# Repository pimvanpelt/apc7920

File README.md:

# APC7920 based on ESP32

This is a project that replaces the older and unmaintained microcontroller
units in APC's famous rack PDU, the AP7920.

## Intro to AP7920

The AP7920 is an 8-port switchable rack mounted power distribution unit. It
features three main components:

1.  A power supply board, which has two 24V power supplies (PSU1 and PSU2) and
    three current sensors (Phase A, B and C). Each current sensor measures
    current from 0..30A AC. When sold in Europe, only one of these is used
    (Phase B).
1.  A microcontroller, based on an older Atmel chip, which features serial
    via an RJ12 plug, and 10/100 Ethernet via an RJ45 plug, and a 7-segment
    display which shows load on Phase B.
1.  A relay board, which features a general purpose I2C GPIO expander based on
    PCF8574, and eight 24V relays, one for each port on the front.

The design of this PDU is rather well done, with two power supplies, and a 
decoupled control plane. The wiring is of high quality, even after many
years of service the components are still in pristine shape. Shrink wrap
is used on the wiring for extra safety and the solder quality is very high.

If the microcontroller reboots or fails, the I2C GPIO expander stays put.
This allows operators to upgrade/reboot/tinker-with the management board
without interrupting service to the load.

### Pinouts

#### Power Supply Board

The power supply board has a 10-pin 2mm pitch connector. It exposes the two
24V power supplies, each with their own ground, and the three current sensors,
with their own separate common ground.

The black wire on the ribbon cables is Pin1. 

Pin | Meaning | Pin | Meaning
--- | --- | --- | ---
1 | I-Sens Phase C | 2 | I-Sens GND
3 | I-Sens Phase A | 4 | I-Sens GND
5 | +24V PSU1 | 6 | +24V PSU1
7 | I-Sens Phase B | 8 | GND PSU1
9 | GND PSU2 | 10 | +24V PSU2

It's worth pointing out that on the power supply board, all ground planes
are separated (so there's one ground pin for PSU1, one for PSU2 and one for
the current sensors).

#### Relay Board

The relay board has a 10-pin 2mm pitch connector. It exposes the I2C chip
which takes common `SDA`, `SDL`, `3.3V` and `GND` pins, and exposes three
address pins `ADDR0`, `ADDR1`, and `ADDR2`. This is presumably done so that
the microcontroller can address up to 8 of these relay boards. It also takes
24V in, which is used to drive the relays.

Pin | Meaning | Pin | Meaning
--- | --- | --- | ---
1 | GND | 2 | GND
3 | VDD (3.3V) | 4 | SDA
5 | +24V | 6 | +24V
7 | ADDR0 | 8 | SDL
9 | ADDR1 | 10 | ADDR2

AP7920 only has one expander, so it doesn't really matter which address
the MCU selects.

## Interposer board

This project works by replacing the two ribbon cables that go from the power
supply board and the relay board to the microcontroller. It's designed to
be a plugin replacement -- just remove the connectors from the microcontroller
and plug them into the interposer board instead.

The interposer has a few components. Firstly, there's a DC/DC buck converter
which takes 24V from PSU1 and switches it down to 5V. Then, there's a LDO that
takes the 5V and regulates it down to 3.3V. Lastly, there's an ADC chip that
measures the current on Phase A,B,C and the voltage out of PSU1 and PSU2 by 
using voltage dividers (the ADC runs at 3.3V so at least a 7:1 divider is
necessary to measure the 24V coming out of the PSUs). The 24V rail from PSU2
is looped through to the relay board. It exposes its 3.3V rail to the relay
board as well, to power the GPIO expander and a few other components there.

It exposes its ADC chip on the SPI header (taking `CS`, `CLK`, `DI` and `DO`)
and it exposes the GPIO expander from the relay board on the I2C header
(showing `SDA`, `SDL`). It offers the 5V and 3.3V rails on the PWR header.
This is enough to connect any other microcontroller that speaks I2C and SPI
instead of the microcontroller that comes with the AP7920 itself. The
interposer assumes only one PCF8574 chip, so it ties all three address pins
`ADDR0`, `ADDR1` and `ADDR2` to `GND`.

The interposer also ties `GND` together from both PSUs, as the original
microcontroller also does that. It has a solder pad (J4) that allows the
current sensor ground to be tied to the main ground as well. In production,
all four solder pads (J1..J4) should be soldered closed. This connects the
current sensor output to the ADC. You can measure the voltage between J4
and J1..J3 to see the current sensed on Phase A..C.

**NOTE** - There is a design flaw in the PCB as it assumes the current
sensor common should be tied to ground, which is not the case. It should be
tied to `VCC/2` so that the signal of the current transformer outputs hovers
between 0-3.3V instead of -1.65-1.65V. A new version is upcoming :)

### BOM

The following components are readily available on Mouser and Digikey. The
full bill of materials for the interposer is as such:

*   R1,R3: 10K Ohm -- voltage divider
*   R2,R4: 75K Ohm -- voltage divider (7:1 minimum)
*   R5,R6: 10K Ohm -- pullup for I2C, optional
*   R7: 220 Ohm -- for blue LED
*   D1: Blue LED 
*   C1: 22uF Tantalum 35V
*   C2,C3: 10uF Tantalum 16V
*   U1: MCP3208 -- 150mil SOIC (Microchip)
*   U2: TSR1-2450 (Traco Power)
*   X1, X2: 5x2 pin 2mm spaced header
*   J1, J2: 3x1 pin 2.54mm spaced header
*   J3: 5x1 pin 2.54mm spaced header

## ESP32 / ESP8266

There are two chips we have to interface with:

*   MCP3208 [datasheet](media/MCP3208.pdf); [driver](https://github.com/mongoose-os-libs/mcp320x-spi)
*   PCF8574 [datasheet](media/PCF8574.pdf); [driver](https://github.com/mongoose-os-libs/pcf8574-i2c)

Libraries for these two chips are readily available for Arduino, but I've
ported them as well to [Mongoose OS](https://mongoose-os.com/) which is my
development platform of choice. This makes writing the program really easy.

### Source Code

See the [firmware](firmware/README.md) directory for information on the firmware.

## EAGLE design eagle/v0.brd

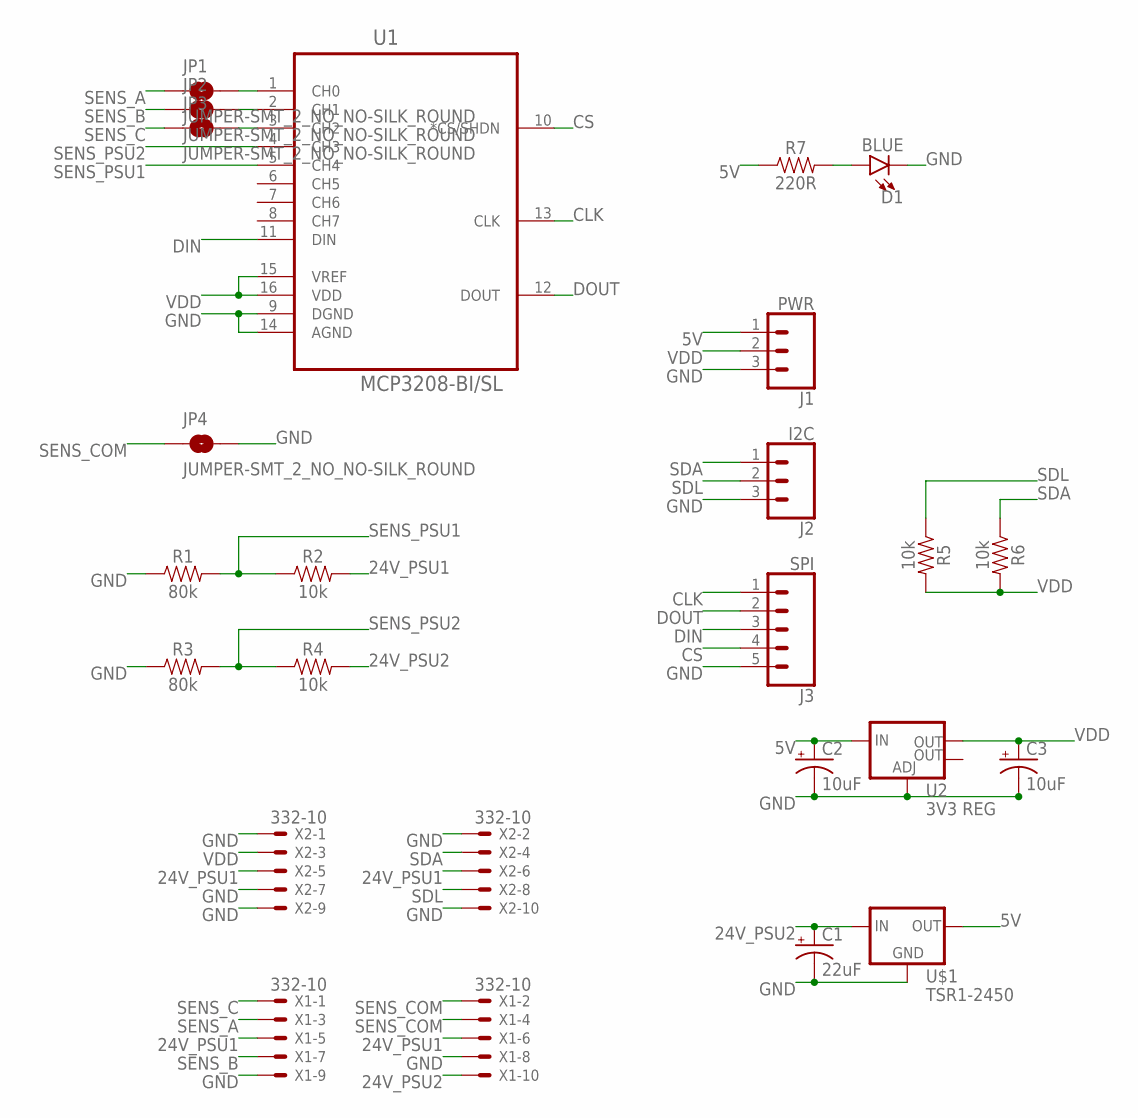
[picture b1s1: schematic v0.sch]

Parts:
C1: 22uF; EIA3216
C2, C3: 10uF; EIA3216
D1: BLUE; LED-0603
J1: PWR; 1X03
J2: I2C; 1X03
J3: SPI; 1X05
JP1, JP2, JP3, JP4: JUMPER-SMT_2_NO_NO-SILK_ROUND; SMT-JUMPER_2_NO_NO-SILK_ROUND
R1, R3: 80k; 0805
R2, R4, R5, R6: 10k; 0805
R7: 220R; 0805
U1: MCP3208-BI/SL; SOIC127P600X175-16N
U2: 3V3 REG; SOT223
U$1: TSR1-2450
X1, X2: 332-10

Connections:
5V: C2.+, J1.1, R7.1, U2.3 (IN), U$1.3 (OUT)
24V_PSU1: R2.2, X1.5, X1.6, X2.5, X2.6
24V_PSU2: C1.+, R4.2, U$1.1 (IN), X1.10
CLK: J3.1, U1.13 (CLK)
CS: J3.4, U1.10 (*CS/SHDN)
DIN: J3.3, U1.11 (DIN)
DOUT: J3.2, U1.12 (DOUT)
GND: C1.-, C2.-, C3.-, D1.C, J1.3, J2.3, J3.5, JP4.2, R1.1, R3.1, U1.9 (DGND), U1.14 (AGND), U2.1 (ADJ), U$1.2 (GND), X1.8, X1.9, X2.1, X2.2, X2.7, X2.9, X2.10
unnamed: JP1.2, U1.1 (CH0)
unnamed: JP2.2, U1.2 (CH1)
unnamed: JP3.2, U1.3 (CH2)
unnamed: D1.A, R7.2
SDA: J2.1, R6.1, X2.4
SDL: J2.2, R5.1, X2.8
SENS_A: JP1.1, X1.3
SENS_B: JP2.1, X1.7
SENS_C: JP3.1, X1.1
SENS_COM: JP4.1, X1.2, X1.4
SENS_PSU1: R1.2, R2.1, U1.5 (CH4)
SENS_PSU2: R3.2, R4.1, U1.4 (CH3)
VDD: C3.+, J1.2, R5.2, R6.2, U1.15 (VREF), U1.16 (VDD), U2.2 (OUT), X2.3

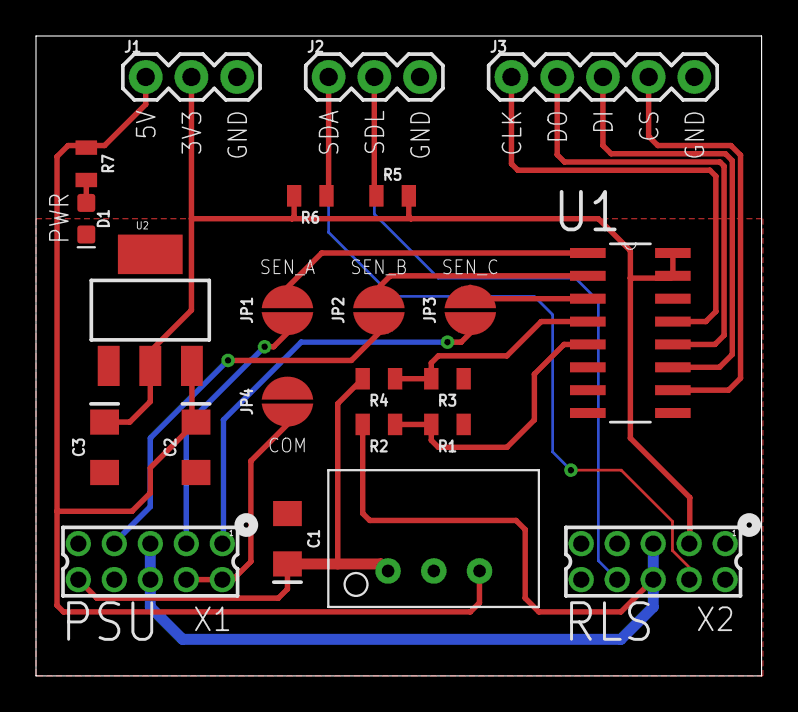
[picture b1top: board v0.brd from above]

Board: 2 copper layers, 40.3 x 35.5 mm, 23 parts (0 on the bottom side), 21 nets.

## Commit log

2018-09-16 Add v0 of the PCB
2018-09-16 Add some starting doco.
2018-09-16 Add picture of AP7920
2018-09-16 Add vendors to BOM -- add Traco buck converter
2018-09-16 Some clarifications.
2018-09-16 Add clarifications to physical build
2018-09-16 Add datasheets; Allude to drivers (to be written)
2018-09-16 Fix typo in PCF chip
2018-09-16 Add image for interposer.
2018-09-16 Crop interposer png
2018-09-16 Fix size of interposer PNG
2018-09-16 Fix cropping to size
2018-09-16 kramdown format for image size
2018-09-16 Manually resize image :)
2018-09-16 Empty firmware skeleton for ESP32
2018-09-16 link in firmware README from main README
2018-09-16 Add skeleton code
    - Commplete mos.yml with config variables and libraries
    - RPC handlers for Channel.{Set,Get,Toggle} in rpc.[ch]
    - Mostly empty channel.[ch]
2018-09-16 Add channel_init(); Remove include/ap7920.h
2018-09-16 Add more skeleton
    - add MCP320X driver -- to be published upstream
    - add PCF8574 driver -- to be published upstream
    - add ADC stubs and adc_init();
    - remove SPI/I2C from main mos.yml -- they will be pulled in by the
    drivers
2018-09-16 Add create()/destroy() methods for MCP320x
2018-09-16 Add create()/destroy() methods for PCF8574
2018-09-16 Add implementation of PCF8574 based on datasheet - only one register (read from reg 0x01, write 1 byte)
2018-09-16 Uncrustify
2018-09-16 Cleanup
    - call _read() on creation, to read the state of the pins.
    - do not reset state on set_mode(); and do not call _write() there.
    - add _validpin() to clean up a bit.
2018-09-16 Fix bug in toggle() -- return back the bit value of dev->_output, not of the returnvalue of _write()
2018-09-21 Add DAC wave generator; lazily initialize i2s RX
2018-09-21 Tinker with I2S - we now have 4 channels read simultaneously at 4KHz
2018-09-21 Play with ADC2 - let it move around
2018-09-21 New monitor all 8 ADC channels! Grab some stats per channel per measurement cycle
2018-09-21 Remove ESP8266 from build targets, we are using I2S and CW generator, specific to ESP32
2018-09-21 Add http-server
2018-09-21 Add some stats counters to i2c_scanner (to be exported by Prometheus)
2018-09-21 Add ringbuffer of size 16; Move stats printing to a 5s timer, so it's less chatty
2018-09-21 Run i2c_scanner at idle priority and add runtime info in a note
2018-09-22 Add UDP mirror for I2S samples
2018-09-22 Disable UDP mirroring by default
2018-09-22 Allow Channel.Get to be called w/o args, in which case we return all channels
2018-09-22 Update README with a note on the CT ADC interaction
2018-09-22 Add Prometheus exporter for I2S Scanner
2018-09-23 Handle uint32_t overflow on s_stats counters
2018-09-23 Add some taskYIELD() to share CPU
2018-09-23 Remove core files - add core-* to .gitignore
2018-09-25 Rewrite DAC task to mgos timer
2018-09-25 Clean up headers that are no longer needed.
2018-09-25 Reduce timer to 5Hz, so we ~always have an event ready to consume
2018-09-25 Unroll the inner loops for readability (return if no event; return if event is not RX)

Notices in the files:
parts and their libraries:
SparkFun-Jumpers: Licensing: Creative Commons ShareAlike 4.0 International - https://creativecommons.org/licenses/by-sa/4.0
